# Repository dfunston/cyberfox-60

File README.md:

# cyberfox-60
An feature packed ergosplit keyboard with extra keys

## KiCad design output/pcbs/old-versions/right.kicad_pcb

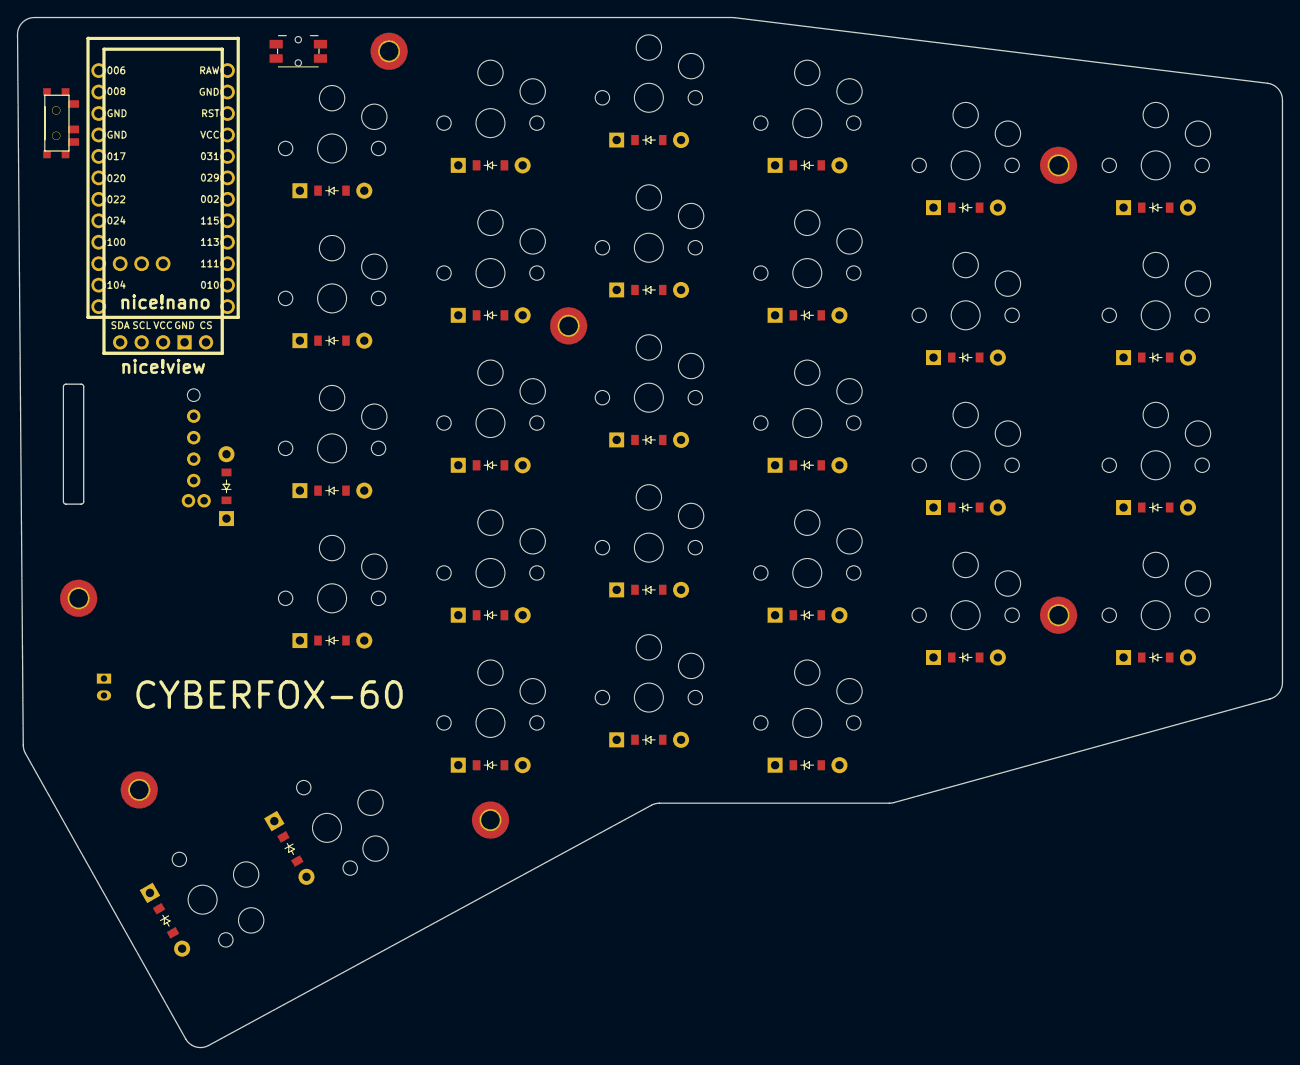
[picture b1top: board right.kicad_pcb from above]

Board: 2 copper layers, 149.7 x 121.9 mm, 71 parts (0 on the bottom side), 48 nets, no tracks yet.

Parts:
B1: Panasonic_EVQPUL_EVQPUC
D1, D2, D3, D4, D5, D6, D7, D8, D9, D10, D11, D12, D13, D14, D15, D16, D17, D18, D19, D20, D21, D22, D23, D24, D25, D26, D27, D28, D29, D30: ComboDiode
JST1: JST_PH_S2B-PH-K_02x2.00mm_Angled
MCU1: nice_nano
S1, S2, S3, S4, S5, S6, S7, S8, S9, S10, S11, S12, S13, S14, S15, S16, S17, S18, S19, S20, S21, S22, S23, S24, S25, S26, S27, S28, S29: PG1350
T1: SPDT_C128955
_2, _3, _4, _5, _6, _7, _8: HOLE_M2
niceView1: niceView; niceView_headers

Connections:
GND: B1.1, JST1.2, MCU1.3, MCU1.4, MCU1.23, niceView1.2
P002: D2.1, D6.1, D11.1, D16.1, D21.1, D25.1, MCU1.18
P009: MCU1.13, S24.1, S25.1, S26.1, S27.1, S29.1
P010: MCU1.14, S20.1, S21.1, S22.1, S23.1, S28.1
P011: MCU1.10, S1.1, S2.1, S3.1, S4.1
P017: MCU1.5, niceView1.5
P020: MCU1.6, niceView1.4
P022: MCU1.7, niceView1.1
P029: D3.1, D7.1, D12.1, D17.1, D22.1, D26.1, MCU1.19
P031: D4.1, D8.1, D13.1, D18.1, D23.1, D27.1, MCU1.20
P104: MCU1.11, S5.1, S6.1, S7.1, S8.1, S9.1
P106: MCU1.12, S10.1, S11.1, S12.1, S13.1, S14.1
P111: MCU1.15, S15.1, S16.1, S17.1, S18.1, S19.1
P113: D9.1, D14.1, D19.1, D28.1, D29.1, D30.1, MCU1.16
P115: D1.1, D5.1, D10.1, D15.1, D20.1, D24.1, MCU1.17
POS: JST1.1, T1.1
RAW: MCU1.24, T1.2
RST: B1.2, MCU1.22
VCC: MCU1.21, niceView1.3
mirror_extra_cluster: D29.2, S29.2
mirror_index_bottom: D20.2, S20.2
mirror_index_home: D21.2, S21.2
mirror_index_mod: D19.2, S19.2
mirror_index_num: D23.2, S23.2
mirror_index_top: D22.2, S22.2
mirror_inner_bottom: D24.2, S24.2
mirror_inner_home: D25.2, S25.2
mirror_inner_num: D27.2, S27.2
mirror_inner_top: D26.2, S26.2
mirror_middle_bottom: D15.2, S15.2
mirror_middle_home: D16.2, S16.2
mirror_middle_mod: D14.2, S14.2
mirror_middle_num: D18.2, S18.2
mirror_middle_top: D17.2, S17.2
mirror_outer_bottom: D1.2, S1.2
mirror_outer_home: D2.2, S2.2
mirror_outer_num: D4.2, S4.2
mirror_outer_top: D3.2, S3.2
mirror_pinky_bottom: D5.2, S5.2
mirror_pinky_home: D6.2, S6.2
mirror_pinky_num: D8.2, S8.2
mirror_pinky_top: D7.2, S7.2
mirror_ring_bottom: D10.2, S10.2
mirror_ring_home: D11.2, S11.2
mirror_ring_mod: D9.2, S9.2
mirror_ring_num: D13.2, S13.2
mirror_ring_top: D12.2, S12.2
mirror_space_cluster: D28.2, S28.2

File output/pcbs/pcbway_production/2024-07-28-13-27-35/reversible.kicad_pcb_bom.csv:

Designator,Quantity,Value,Footprint,Package,MPN,DNP,Mount_Type
,1,EVQWGD001,RollerEncoder_Panasonic_EVQWGD001,,,,tht
"D1, D10, D11, D12, D13, D14, D15, D16, D17, D18, D19, D2, D20, D21, D22, D23, D24, D25, D26, D27, D28, D29, D3, D30, D4, D5, D6, D7, D8, D9",30,,diode_tht_sod123,,,,tht
DISP1,1,,display_nice_view,,,,tht
JST1,1,,battery_connector_jst_ph_2,,,,tht
MCU1,1,,mcu_nice_nano,,,,tht
"MH1, MH2, MH3, MH4, MH5, MH6, MH7",7,,mounting_hole_npth,,,,tht
PWR1,1,,power_switch_smd_side,,,,smt
RST1,1,,reset_switch_smd_side,,,,smt
"S1, S10, S11, S12, S13, S14, S15, S16, S17, S18, S19, S2, S20, S21, S22, S23, S24, S25, S26, S27, S28, S29, S3, S4, S5, S6, S7, S8, S9",29,,switch_choc_v1_v2,,,,tht

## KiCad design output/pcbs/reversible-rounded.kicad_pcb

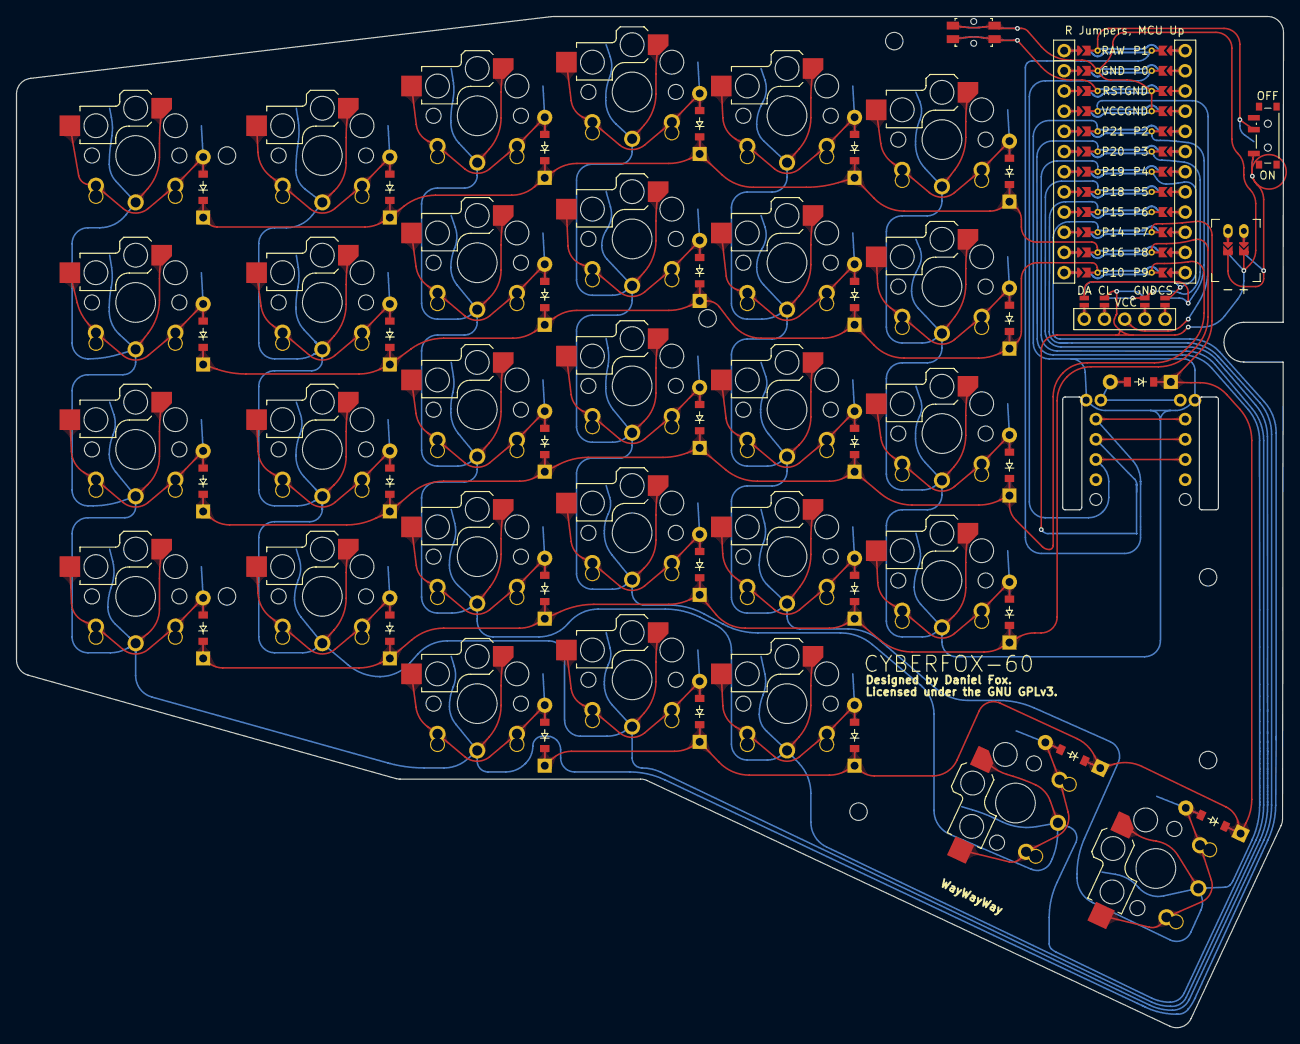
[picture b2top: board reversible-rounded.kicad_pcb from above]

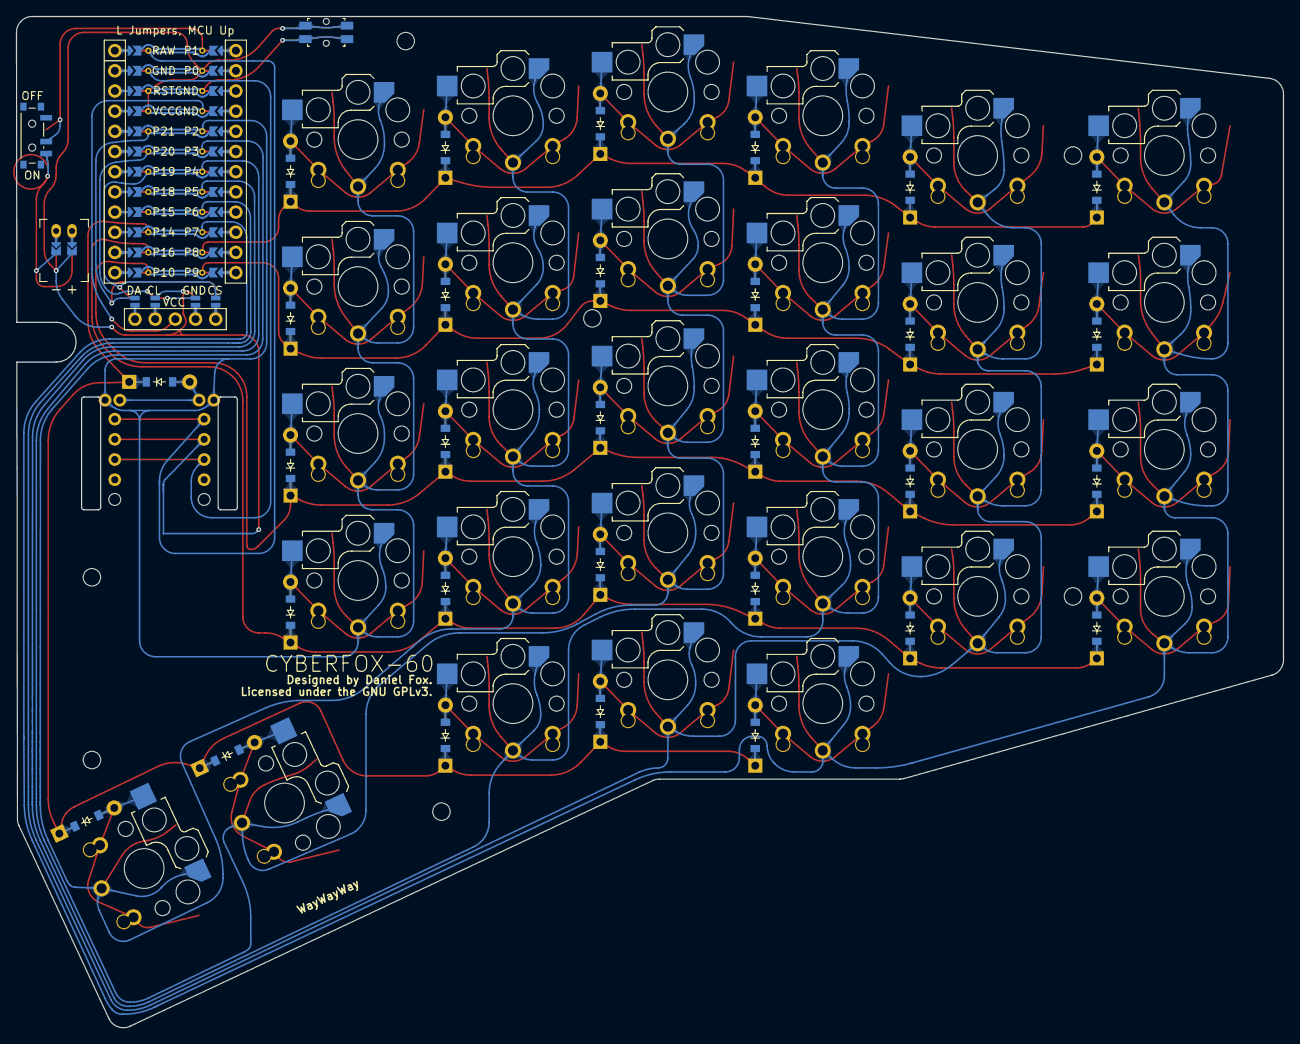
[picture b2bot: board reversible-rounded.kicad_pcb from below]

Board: 2 copper layers, 159.5 x 127.3 mm, 71 parts (59 on the bottom side), 54 nets.

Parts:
D1, D2, D3, D4, D5, D6, D7, D8, D9, D10, D11, D12, D13, D14, D15, D16, D17, D18, D19, D20, D21, D22, D23, D24, D25, D26, D27, D28, D29, D30: diode_tht_sod123
DISP1: display_nice_view
JST1: battery_connector_jst_ph_2
MCU1: mcu_nice_nano
MH1, MH2, MH3, MH4, MH5, MH6, MH7: mounting_hole_npth
PWR1: power_switch_smd_side
RST1: reset_switch_smd_side
S1, S2, S3, S4, S5, S6, S7, S8, S9, S10, S11, S12, S13, S14, S15, S16, S17, S18, S19, S20, S21, S22, S23, S24, S25, S26, S27, S28, S29: switch_choc_v1_v2

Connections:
BAT_P: JST1.1, PWR1.1, PWR1.3
DISP1_1: DISP1.1, DISP1.10, DISP1.23
DISP1_2: DISP1.2, DISP1.11, DISP1.22
DISP1_4: DISP1.4, DISP1.12, DISP1.21
DISP1_5: DISP1.5, DISP1.13, DISP1.20
GND: DISP1.15, DISP1.25, JST1.2, MCU1.103, MCU1.104, MCU1.123, RST1.1, RST1.3
JST1_1: JST1.11, JST1.21, JST1.31
JST1_2: JST1.12, JST1.22, JST1.32
P2: DISP1.14, DISP1.24, MCU1.105
P3: DISP1.16, DISP1.26, MCU1.106
P4: DISP1.17, DISP1.27, MCU1.107
P7: D9.1, D14.1, D19.1, D28.1, D29.1, D30.1, MCU1.110
P8: D1.1, D5.1, D10.1, D15.1, D20.1, D24.1, MCU1.111
P9: D2.1, D6.1, D11.1, D16.1, D21.1, D25.1, MCU1.112
P10: D3.1, D7.1, D12.1, D17.1, D22.1, D26.1, MCU1.113
P14: MCU1.115, S1.1, S1.2, S2.1, S2.2, S3.1, S3.2, S4.1, S4.2, S9.1, S9.2
P15: MCU1.116, S5.1, S5.2, S6.1, S6.2, S7.1, S7.2, S8.1, S8.2, S14.1, S14.2
P16: D4.1, D8.1, D13.1, D18.1, D23.1, D27.1, MCU1.114
P18: MCU1.117, S10.1, S10.2, S11.1, S11.2, S12.1, S12.2, S13.1, S13.2, S19.1, S19.2
P19: MCU1.118, S15.1, S15.2, S16.1, S16.2, S17.1, S17.2, S18.1, S18.2, S28.1, S28.2
P20: MCU1.119, S20.1, S20.2, S21.1, S21.2, S22.1, S22.2, S23.1, S23.2, S29.1, S29.2
P21: MCU1.120, S24.1, S24.2, S25.1, S25.2, S26.1, S26.2, S27.1, S27.2
RAW: MCU1.124, PWR1.2
RST: MCU1.122, RST1.2, RST1.4
VCC: DISP1.3, MCU1.121
extra_cluster: D29.2, S29.1, S29.2
index_bottom: D20.2, S20.1, S20.2
index_home: D21.2, S21.1, S21.2
index_mod: D19.2, S19.1, S19.2
index_num: D23.2, S23.1, S23.2
index_top: D22.2, S22.1, S22.2
inner_bottom: D24.2, S24.1, S24.2
inner_home: D25.2, S25.1, S25.2
inner_num: D27.2, S27.1, S27.2
inner_top: D26.2, S26.1, S26.2
middle_bottom: D15.2, S15.1, S15.2
middle_home: D16.2, S16.1, S16.2
middle_mod: D14.2, S14.1, S14.2
middle_num: D18.2, S18.1, S18.2
middle_top: D17.2, S17.1, S17.2
outer_bottom: D1.2, S1.1, S1.2
outer_home: D2.2, S2.1, S2.2
outer_num: D4.2, S4.1, S4.2
outer_top: D3.2, S3.1, S3.2
pinky_bottom: D5.2, S5.1, S5.2
pinky_home: D6.2, S6.1, S6.2
pinky_num: D8.2, S8.1, S8.2
pinky_top: D7.2, S7.1, S7.2
ring_bottom: D10.2, S10.1, S10.2
ring_home: D11.2, S11.1, S11.2
ring_mod: D9.2, S9.1, S9.2
ring_num: D13.2, S13.1, S13.2
ring_top: D12.2, S12.1, S12.2
space_cluster: D28.2, S28.1, S28.2

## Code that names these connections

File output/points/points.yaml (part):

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        autobind: 10
        skip: false
        asym: both
        colrow: pinky_bottom
        name: matrix_pinky_bottom
        tags:
            cap: true
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        autobind: 10
        skip: false
        asym: both
        colrow: pinky_home
        name: matrix_pinky_home
        tags:
            cap: true
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        autobind: 10
        skip: false
        asym: both
        colrow: pinky_top
        name: matrix_pinky_top
        tags:
            cap: true
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        autobind: 10
        skip: false
        asym: both
        colrow: pinky_num
        name: matrix_pinky_num
        tags:
            cap: true
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
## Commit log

2024-07-20 Initial version creation
2024-07-20 Merged cyberfox.yaml into config.yaml This better follows what ergogen is looking for
2024-07-20 Deleted cyberfox.yaml, per last commit
2024-07-21 PCB config is now mostly completed
2024-07-21 Removed file mountinghole.js.1
2024-07-21 A bit more touch-up on the PCB. Things are shaping up, but not yet done.
2024-07-21 Updated .gitignore to ignore .DS_Store files
2024-07-21 Changed from rotary knob to scrollwheel. Further minor refinements.
2024-07-21 Removed autosave file for kicad
2024-07-21 Added screw holes and an extra diode for the scrollwheel
2024-07-21 Deleted auto-generated file
2024-07-22 Starting to trace the PCB
2024-07-22 Slow progress on routing the connections on the left PCB.
2024-07-23 Got the columns routed around the thumb cluster on the left PCB
2024-07-24 New config.yaml using Ceoloide components. The config is being updated to make one reversible PCB rather than separate left and right PCBs. This will ultimately save on cost, but increase complexity 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
2024-07-25 Further refinements to config.yaml
2024-07-25 Updates to the config file. Slowly building to the PCB editing stage.
2024-07-25 Update config.yaml
    Minor updates to component positioning
2024-07-27 More overhaul. TODO: Need to renet the pins.
2024-07-27 Starting to wire the reversible PCB
2024-08-01 The PCB's wiring is completed. May need additional touchup.

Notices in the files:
output/pcbs/reversible-rounded.kicad_pcb:
Licensed under the GNU GPLv3.
